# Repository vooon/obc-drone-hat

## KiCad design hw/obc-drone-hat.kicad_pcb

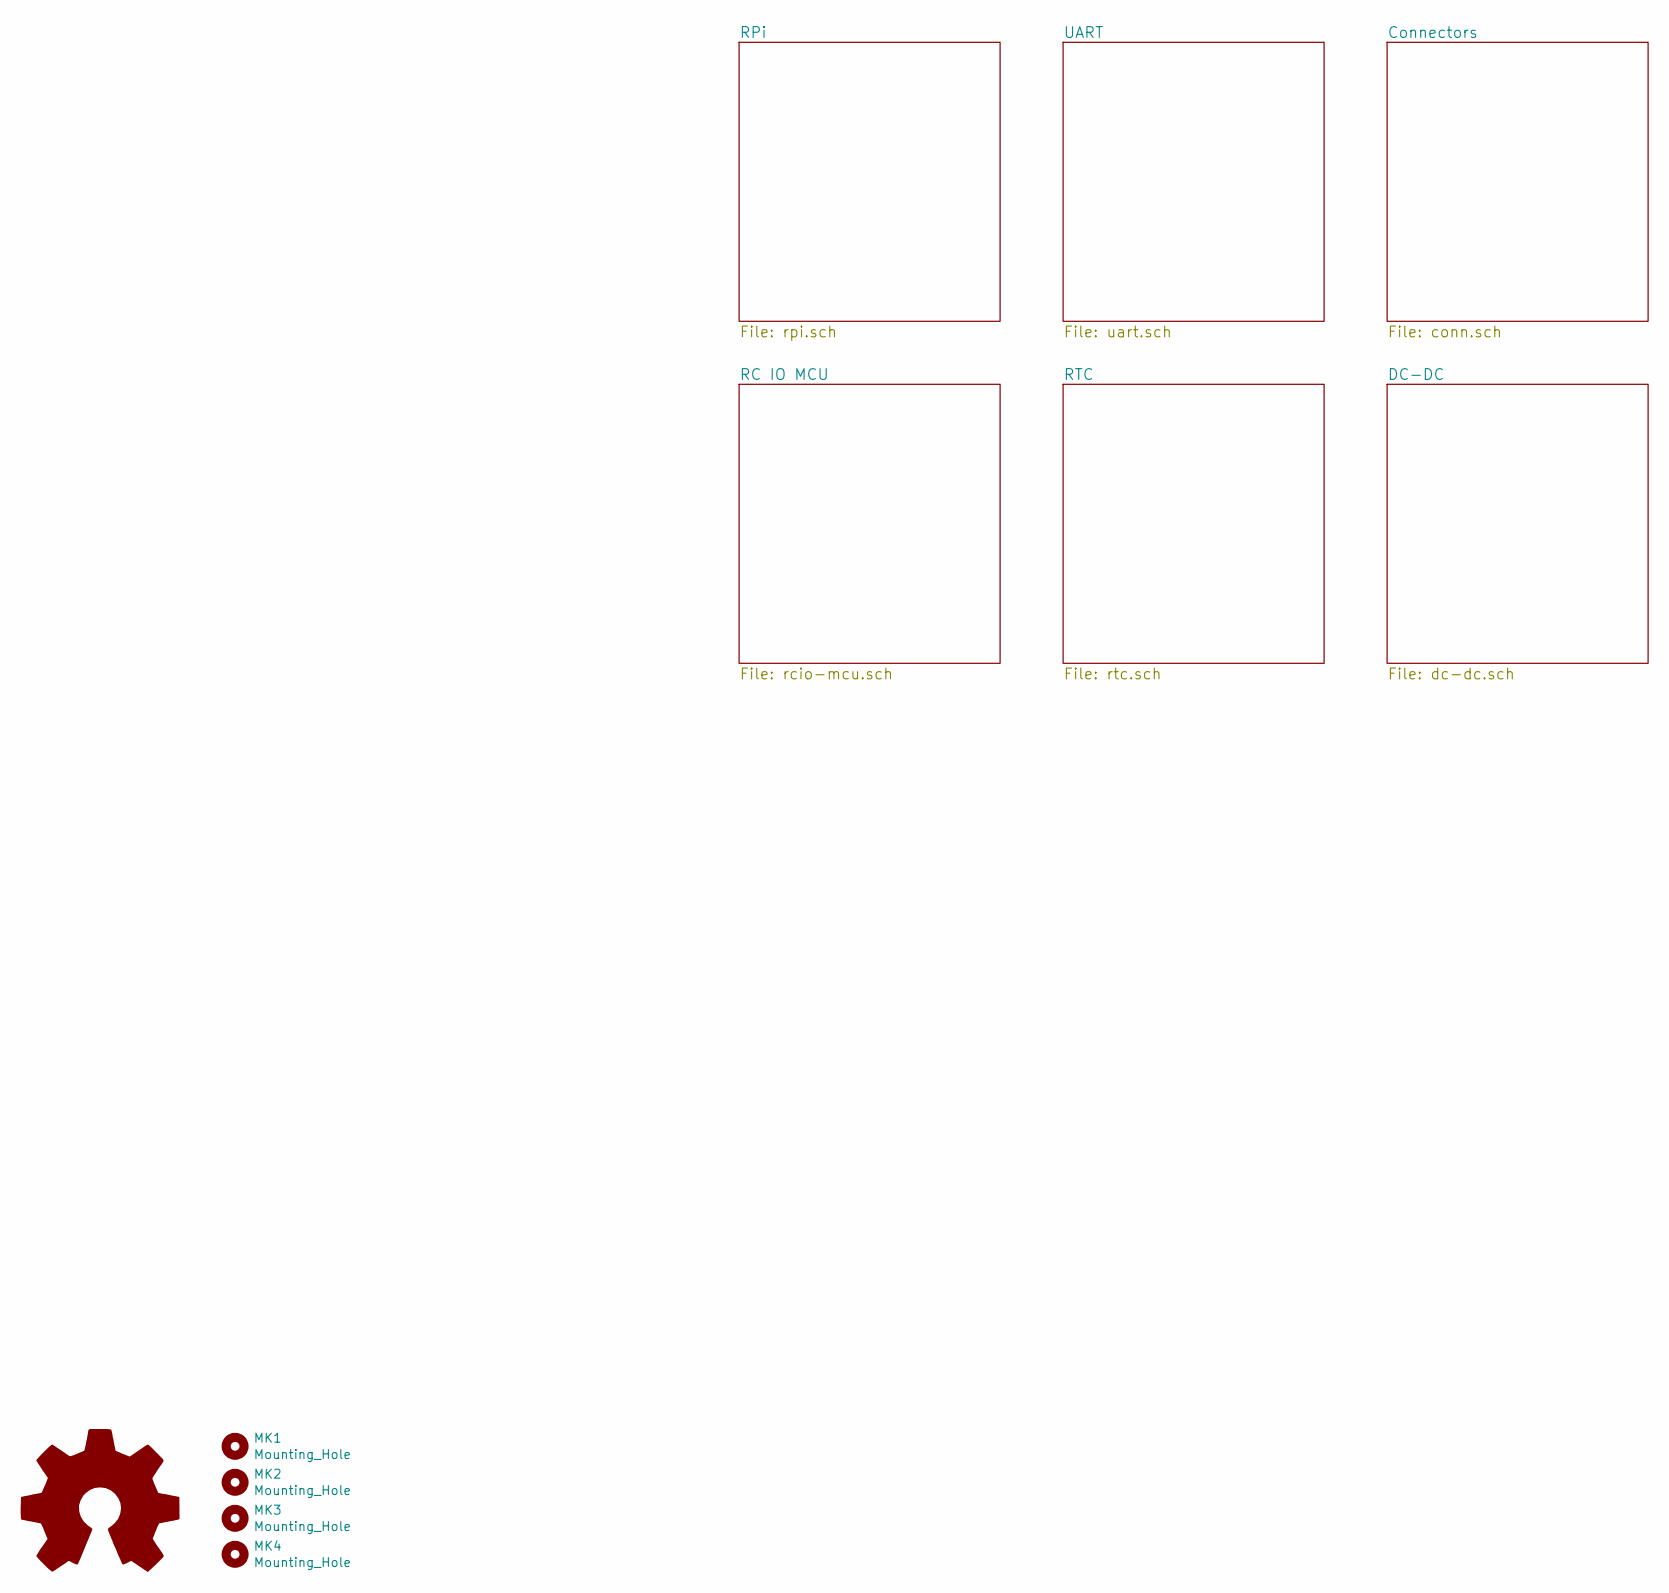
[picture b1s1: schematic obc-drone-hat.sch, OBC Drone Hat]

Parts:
MK1, MK2, MK3, MK4: Mounting_Hole; M2.5_Mounting_Hole

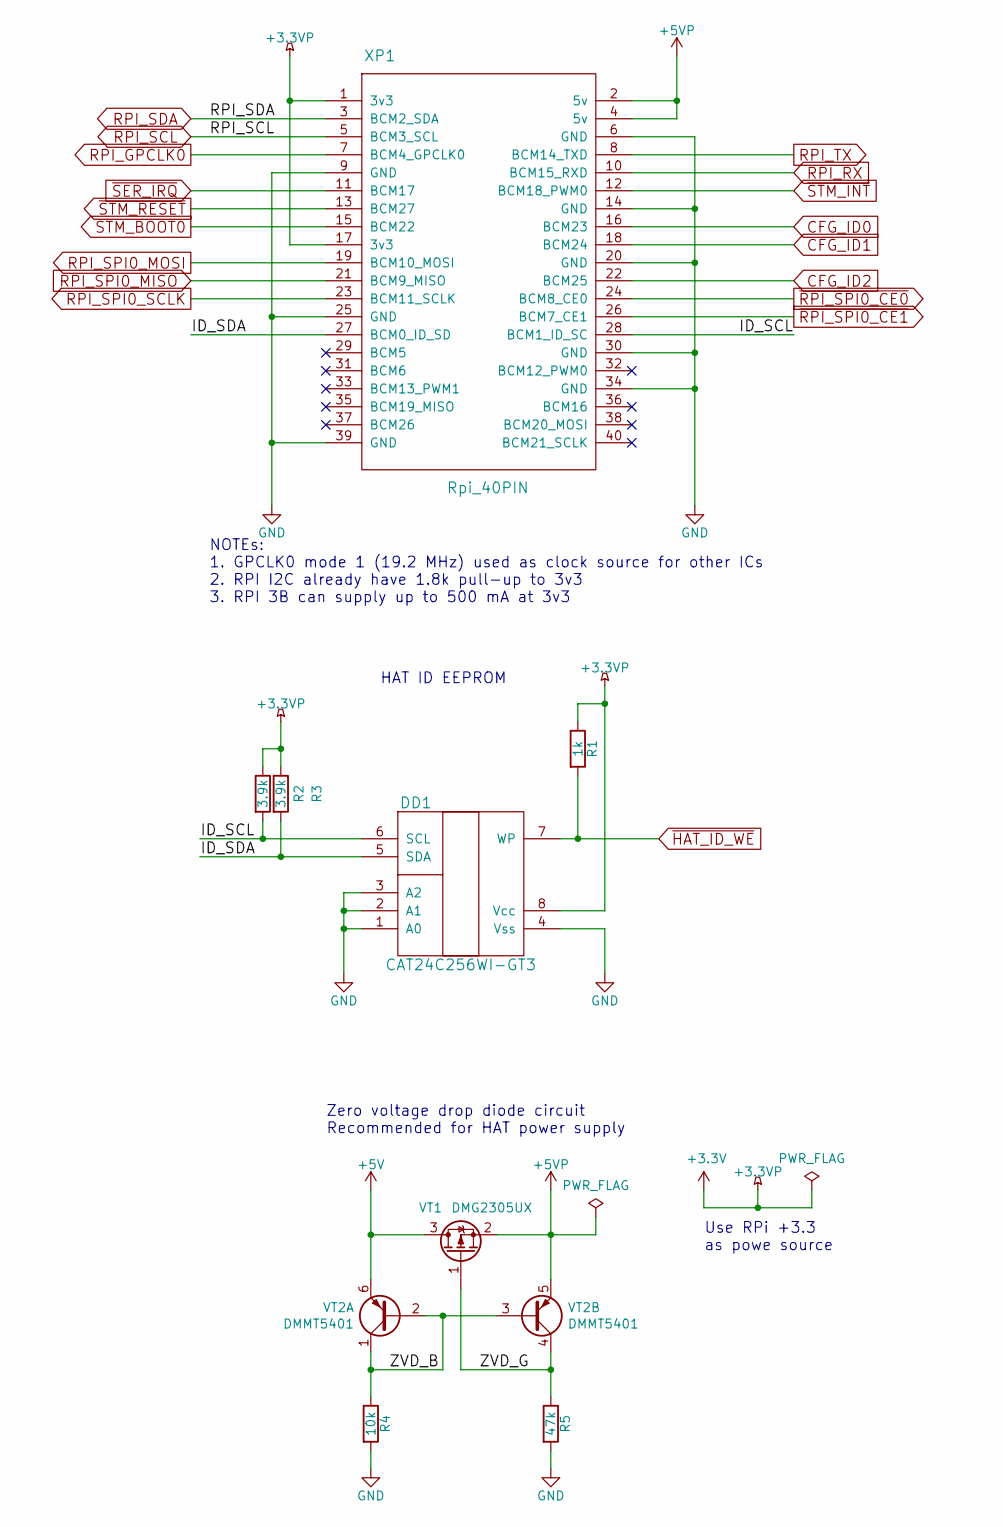
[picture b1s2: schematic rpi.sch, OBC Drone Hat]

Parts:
DD1: CAT24C256WI-GT3; SO-8_5.3x6.2mm_P1.27mm
R1: 1k; R_0603_1608Metric
R2, R3: 3.9k; R_0603_1608Metric
R4: 10k; R_0603_1608Metric
R5: 47k; R_0603_1608Metric
VT1: DMG2305UX; SOT-23_Handsoldering
VT2: DMMT5401; SOT-23-6_Handsoldering
XP1: Rpi_40PIN; RaspberryPi-40Pin_P2.54mm

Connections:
+3.3VP: DD1.8 (Vcc), R1.1, R2.1, R3.1, XP1.1 (3v3), XP1.17 (3v3); also elsewhere on the board
+5VP: VT1.2 (S), VT2.5 (E2), XP1.2 (5v), XP1.4 (5v); also elsewhere on the board
+5Vhat: VT1.3 (D), VT2.6 (E1); also elsewhere on the board
/RPi/ID_SCL: DD1.6 (SCL), R2.2, XP1.28 (BCM1_ID_SC)
/RPi/ID_SDA: DD1.5 (SDA), R3.2, XP1.27 (BCM0_ID_SD)
/RPi/ZVD_B: R4.1, VT2.1 (C1), VT2.2 (B1), VT2.3 (B2)
/RPi/ZVD_G: R5.1, VT1.1 (G), VT2.4 (C2)
CFG_ID0: XP1.16 (BCM23); also elsewhere on the board
CFG_ID1: XP1.18 (BCM24); also elsewhere on the board
CFG_ID2: XP1.22 (BCM25); also elsewhere on the board
GND: DD1.1 (A0), DD1.2 (A1), DD1.3 (A2), DD1.4 (Vss), R4.2, R5.2, XP1.6 (GND), XP1.9 (GND), XP1.14 (GND), XP1.20 (GND), XP1.25 (GND), XP1.30 (GND), XP1.34 (GND), XP1.39 (GND); also elsewhere on the board
RPI_GPCLK0: XP1.7 (BCM4_GPCLK0); also elsewhere on the board
RPI_RX: XP1.10 (BCM15_RXD); also elsewhere on the board
RPI_SCL: XP1.5 (BCM3_SCL); also elsewhere on the board
RPI_SDA: XP1.3 (BCM2_SDA); also elsewhere on the board
RPI_SPI0_MISO: XP1.21 (BCM9_MISO); also elsewhere on the board
RPI_SPI0_MOSI: XP1.19 (BCM10_MOSI); also elsewhere on the board
RPI_SPI0_SCLK: XP1.23 (BCM11_SCLK); also elsewhere on the board
RPI_TX: XP1.8 (BCM14_TXD); also elsewhere on the board
STM_BOOT0: XP1.15 (BCM22); also elsewhere on the board
~HAT_ID_WE: DD1.7 (WP), R1.2; also elsewhere on the board
~RPI_SPI0_CE0: XP1.24 (BCM8_CE0); also elsewhere on the board
~RPI_SPI0_CE1: XP1.26 (BCM7_CE1); also elsewhere on the board
~SER_IRQ: XP1.11 (BCM17); also elsewhere on the board
~STM_INT: XP1.12 (BCM18_PWM0); also elsewhere on the board
~STM_RESET: XP1.13 (BCM27); also elsewhere on the board

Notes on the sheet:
HAT ID EEPROM
NOTEs: 1. GPCLK0 mode 1 (19.2 MHz) used as clock source for other ICs 2. RPI I2C already have 1.8k pull-up to 3v3 3. RPI 3B can supply up to 500 mA at 3v3
Zero voltage drop diode circuit Recommended for HAT power supply
Use RPi +3.3 as powe source

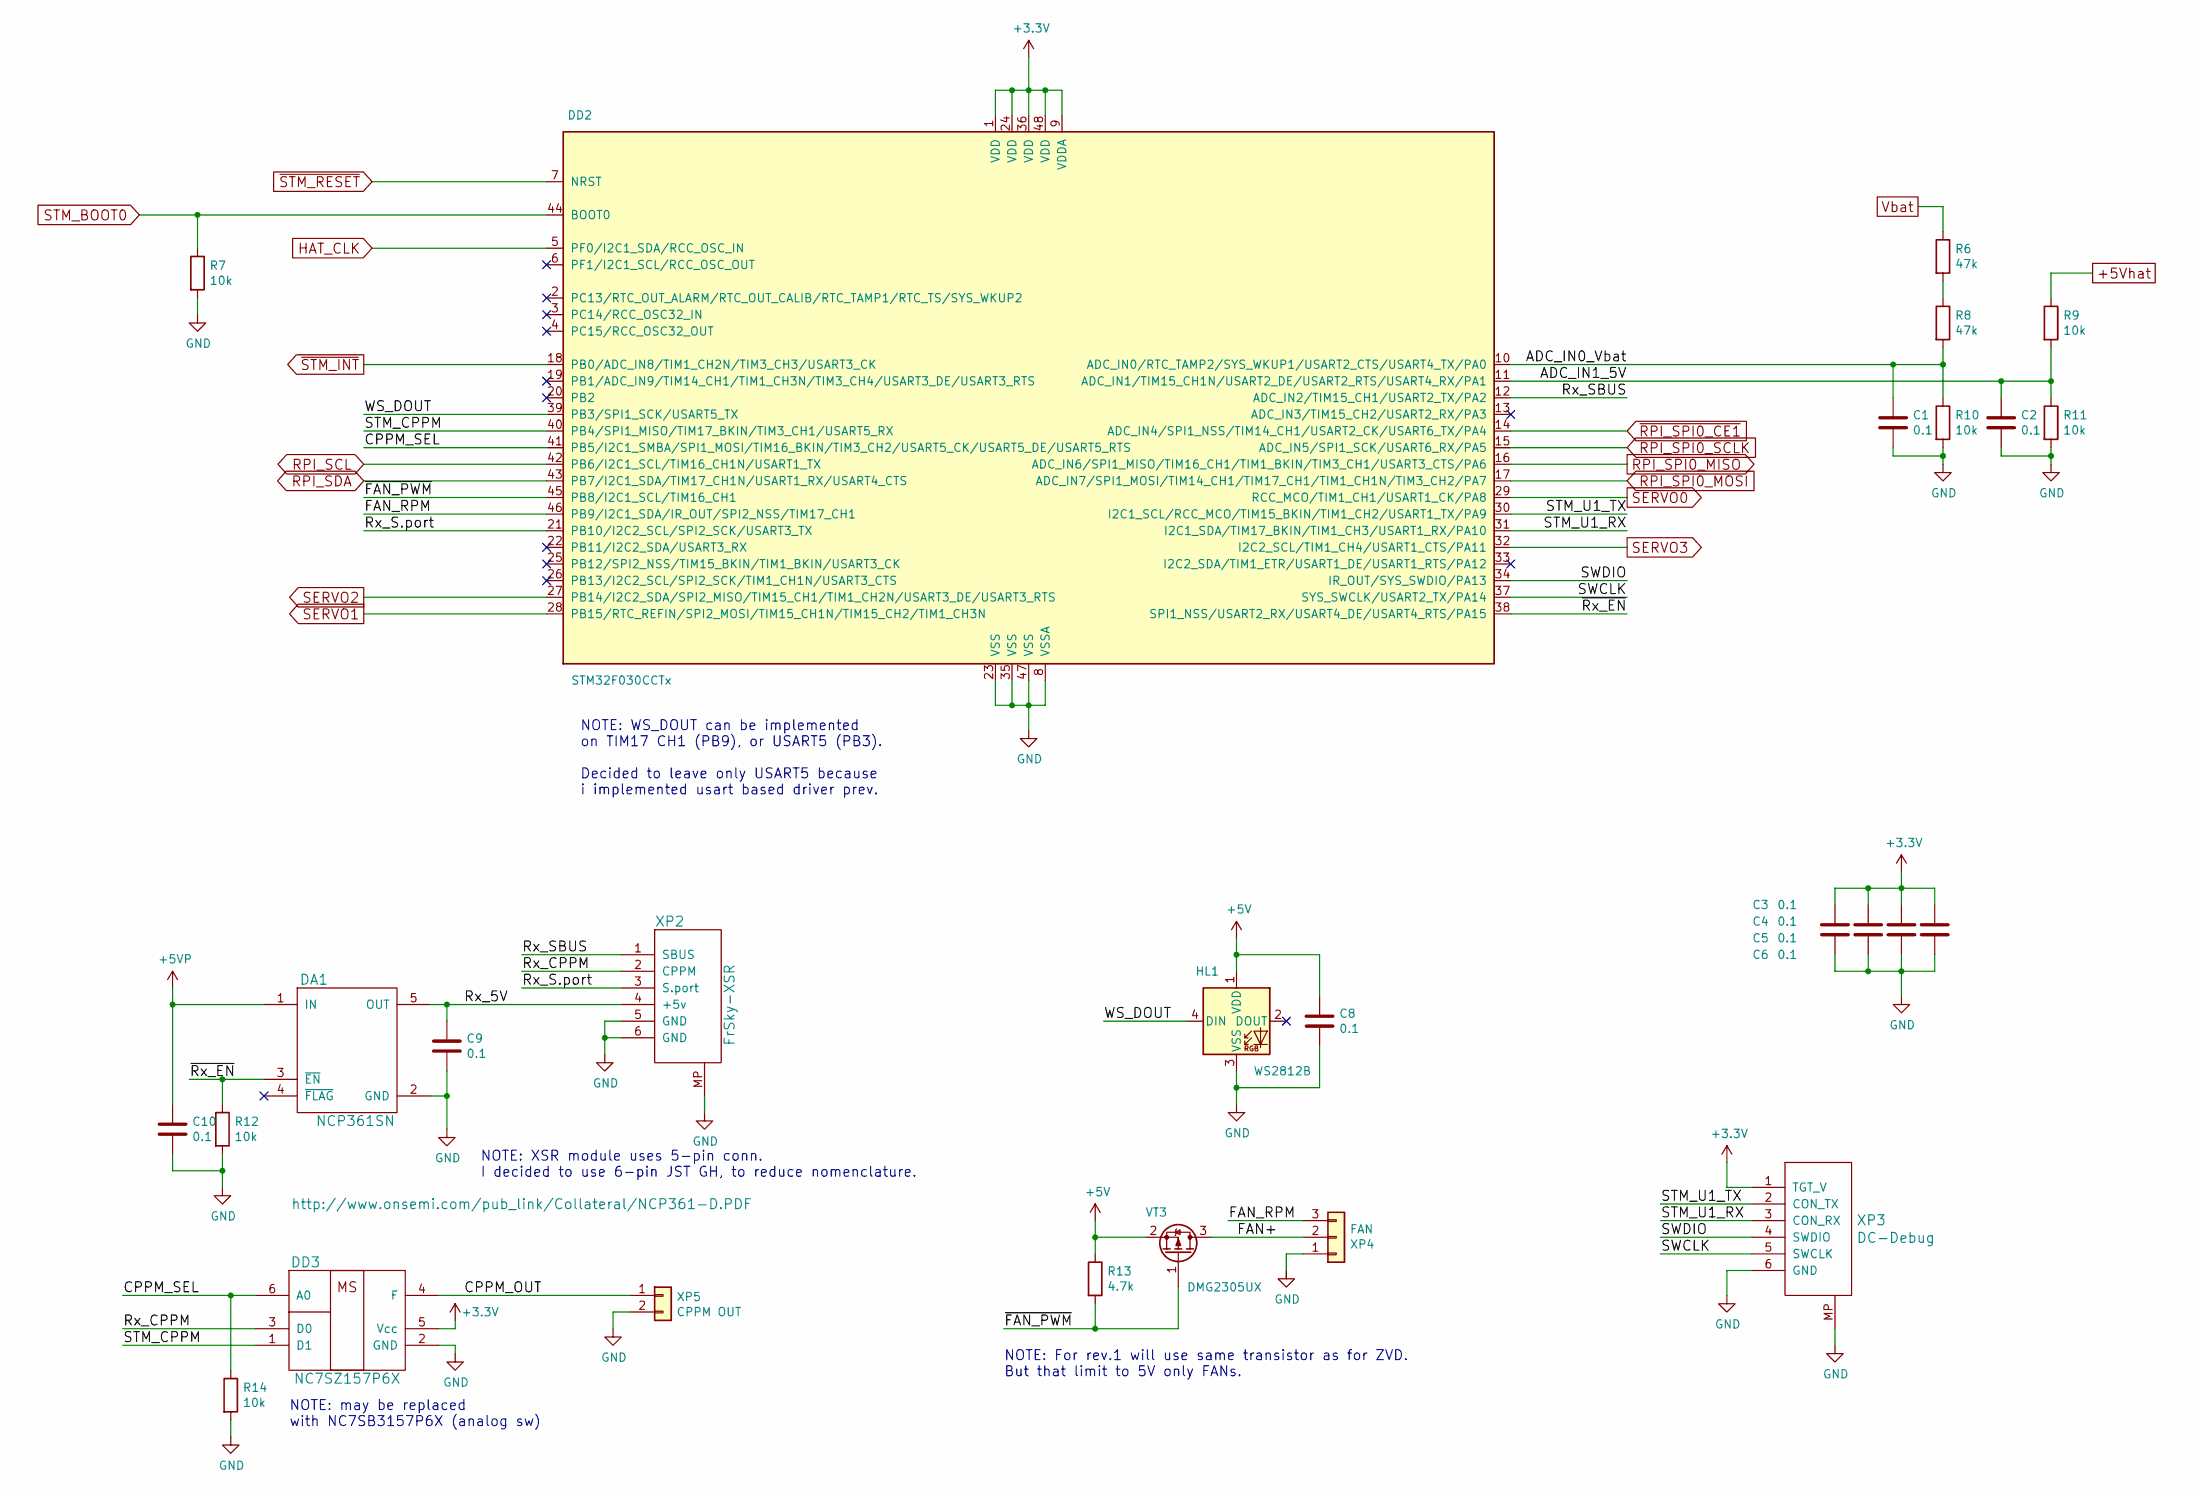
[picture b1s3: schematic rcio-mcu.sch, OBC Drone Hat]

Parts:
C1, C2, C3, C4, C5, C6, C8, C9, C10: 0.1; C_0603_1608Metric
DA1: NCP361SN; SOT-23-5_HandSoldering
DD2: STM32F030CCTx; LQFP-48_7x7mm_P0.5mm
DD3: NC7SZ157P6X; SOT-363_SC-70-6_Handsoldering
HL1: WS2812B; LED_WS2812B_PLCC4_5.0x5.0mm_P3.2mm
R6, R8: 47k; R_0603_1608Metric
R7, R9, R10, R11, R12, R14: 10k; R_0603_1608Metric
R13: 4.7k; R_0603_1608Metric
VT3: DMG2305UX; SOT-23_Handsoldering
XP2: FrSky-XSR; JST_GH_SM06B-GHS-TB_1x06-1MP_P1.25mm_Horizontal
XP3: DC-Debug; JST_GH_BM06B-GHS-TBT_1x06-1MP_P1.25mm_Vertical
XP4: FAN; FanPinHeader_1x03_P2.54mm_Vertical
XP5: CPPM OUT; JST_PH_B2B-PH-K_1x02_P2.00mm_Vertical

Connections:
+3.3VP: C3.1, C4.1, C5.1, C6.1, DD2.1 (VDD), DD2.9 (VDDA), DD2.24 (VDD), DD2.36 (VDD), DD2.48 (VDD), DD3.5 (Vcc), XP3.1 (TGT_V); also elsewhere on the board
+5VP: C10.1, DA1.1 (IN); also elsewhere on the board
+5Vhat: C8.1, HL1.1 (VDD), R9.1, R13.1, VT3.2 (S); also elsewhere on the board
/RC IO MCU/ADC_IN0_Vbat: C1.1, DD2.10 (ADC_IN0/RTC_TAMP2/SYS_WKUP1/USART2_CTS/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), R8.2, R10.1
/RC IO MCU/ADC_IN1_5V: C2.1, DD2.11 (ADC_IN1/TIM15_CH1N/USART2_DE/USART2_RTS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), R9.2, R11.1
/RC IO MCU/CPPM_OUT: DD3.4 (F), XP5.1
/RC IO MCU/CPPM_SEL: DD2.41 (PB5/I2C1_SMBA/SPI1_MOSI/TIM16_BKIN/TIM3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), DD3.6 (A0), R14.1
/RC IO MCU/FAN+: VT3.3 (D), XP4.2
/RC IO MCU/FAN_RPM: DD2.46 (PB9/I2C1_SDA/IR_OUT/SPI2_NSS/TIM17_CH1), XP4.3
/RC IO MCU/Rx_5V: C9.1, DA1.5 (OUT), XP2.4 (+5v)
/RC IO MCU/Rx_CPPM: DD3.3 (D0), XP2.2 (CPPM)
/RC IO MCU/Rx_S.port: DD2.21 (PB10/I2C2_SCL/SPI2_SCK/USART3_TX), XP2.3 (S.port)
/RC IO MCU/Rx_SBUS: DD2.12 (ADC_IN2/TIM15_CH1/USART2_TX/PA2), XP2.1 (SBUS)
/RC IO MCU/STM_CPPM: DD2.40 (PB4/SPI1_MISO/TIM17_BKIN/TIM3_CH1/USART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), DD3.1 (D1)
/RC IO MCU/STM_U1_RX: DD2.31 (I2C1_SDA/TIM17_BKIN/TIM1_CH3/USART1_RX/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), XP3.3 (CON_RX)
/RC IO MCU/STM_U1_TX: DD2.30 (I2C1_SCL/RCC_MCO/TIM15_BKIN/TIM1_CH2/US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), XP3.2 (CON_TX)
/RC IO MCU/SWCLK: DD2.37 (SYS_SWCLK/USART2_TX/PA14), XP3.5 (SWCLK)
/RC IO MCU/SWDIO: DD2.34 (IR_OUT/SYS_SWDIO/PA13), XP3.4 (SWDIO)
/RC IO MCU/WS_DOUT: DD2.39 (PB3/SPI1_SCK/USART5_TX), HL1.4 (DIN)
/RC IO MCU/~FAN_PWM: DD2.45 (PB8/I2C1_SCL/TIM16_CH1), R13.2, VT3.1 (G)
/RC IO MCU/~Rx_EN: DA1.3 (~EN), DD2.38 (SPI1_NSS/USART2_RX/USART4_DE/USART4_RTS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), R12.1
GND: C1.2, C2.2, C3.2, C4.2, C5.2, C6.2, C8.2, C9.2, C10.2, DA1.2 (GND), DD2.8 (VSSA), DD2.23 (VSS), DD2.35 (VSS), DD2.47 (VSS), DD3.2 (GND), HL1.3 (VSS), R7.2, R10.2, R11.2, R12.2, R14.2, XP2.5 (GND), XP2.6 (GND), XP2.MP, XP3.6 (GND), XP3.MP, XP4.1, XP5.2; also elsewhere on the board
HAT_CLK: DD2.5 (PF0/I2C1_SDA/RCC_OSC_IN); also elsewhere on the board
unnamed: R6.2, R8.1
RPI_SCL: DD2.42 (PB6/I2C1_SCL/TIM16_CH1N/USART1_TX); also elsewhere on the board
RPI_SDA: DD2.43 (PB7/I2C1_SDA/TIM17_CH1N/USART1_RX/USART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); also elsewhere on the board
RPI_SPI0_MISO: DD2.16 (ADC_IN6/SPI1_MISO/TIM16_CH1/TIM1_BKIN/T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); also elsewhere on the board
RPI_SPI0_MOSI: DD2.17 (ADC_IN7/SPI1_MOSI/TIM14_CH1/TIM17_CH1/T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); also elsewhere on the board
RPI_SPI0_SCLK: DD2.15 (ADC_IN5/SPI1_SCK/USART6_RX/PA5); also elsewhere on the board
SERVO0: DD2.29 (RCC_MCO/TIM1_CH1/USART1_CK/PA8); also elsewhere on the board
SERVO1: DD2.28 (PB15/RTC_REFIN/SPI2_MOSI/TIM15_CH1N/TIM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); also elsewhere on the board
SERVO2: DD2.27 (PB14/I2C2_SDA/SPI2_MISO/TIM15_CH1/TIM1_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); also elsewhere on the board
SERVO3: DD2.32 (I2C2_SCL/TIM1_CH4/USART1_CTS/PA11); also elsewhere on the board
STM_BOOT0: DD2.44 (BOOT0), R7.1; also elsewhere on the board
Vbat: R6.1; also elsewhere on the board
~RPI_SPI0_CE1: DD2.14 (ADC_IN4/SPI1_NSS/TIM14_CH1/USART2_CK/US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); also elsewhere on the board
~STM_INT: DD2.18 (PB0/ADC_IN8/TIM1_CH2N/TIM3_CH3/USART3_CK); also elsewhere on the board
~STM_RESET: DD2.7 (NRST); also elsewhere on the board

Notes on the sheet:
NOTE: XSR module uses 5-pin conn. I decided to use 6-pin JST GH, to reduce nomenclature.
NOTE: may be replaced with NC7SB3157P6X (analog sw)
NOTE: For rev.1 will use same transistor as for ZVD. But that limit to 5V only FANs.
NOTE: WS_DOUT can be implemented on TIM17 CH1 (PB9), or USART5 (PB3). Decided to leave only USART5 because i implemented usart based driver prev.

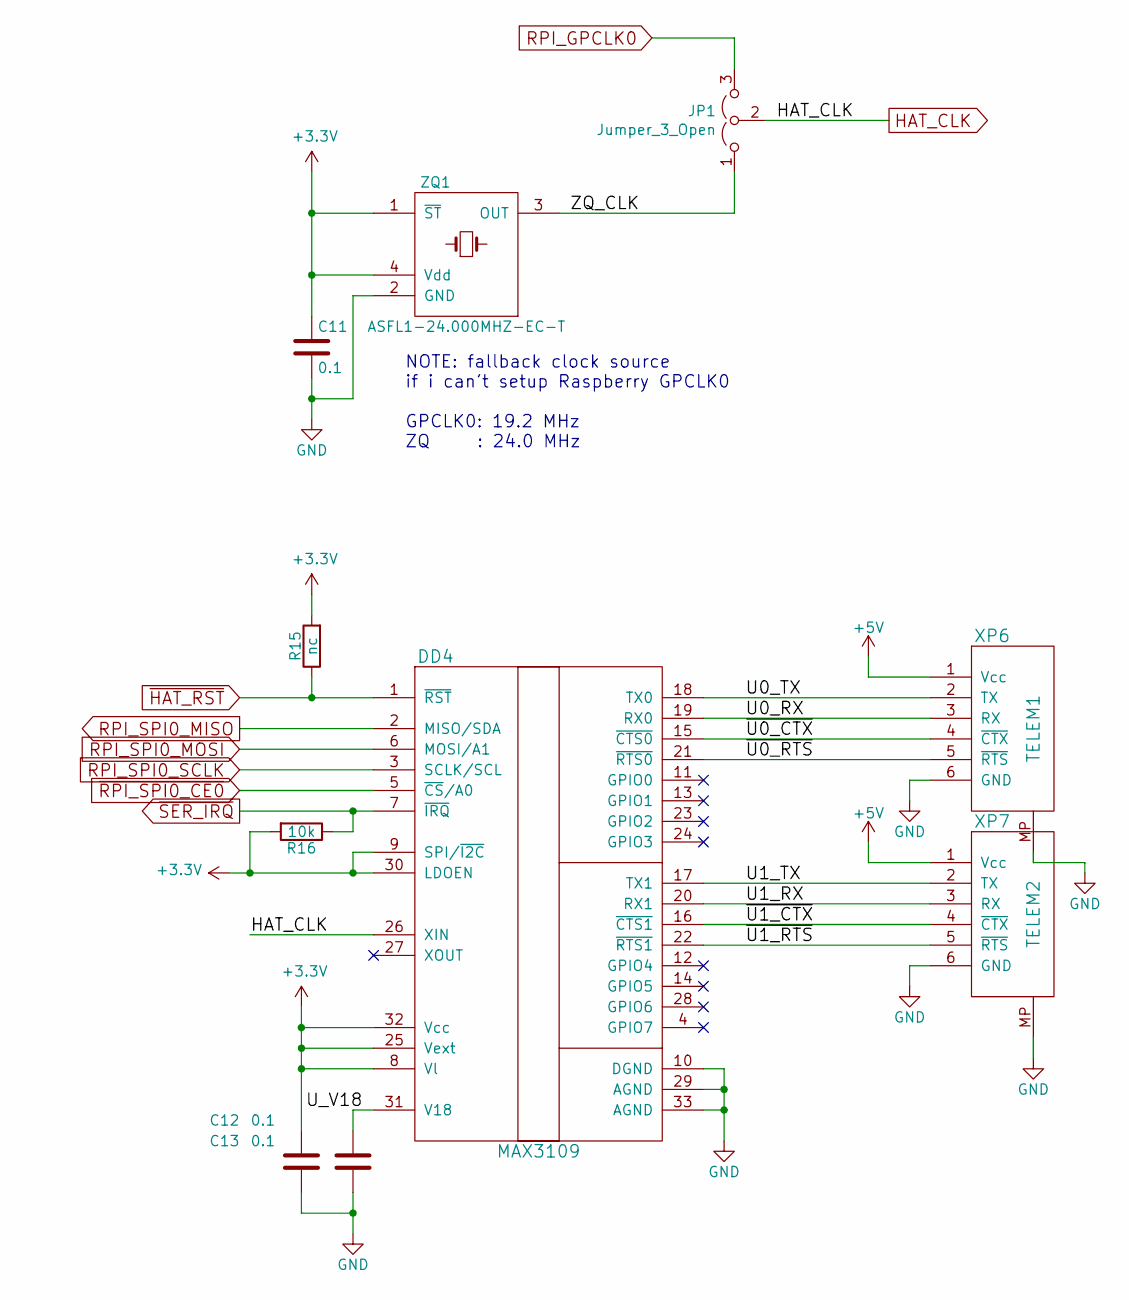
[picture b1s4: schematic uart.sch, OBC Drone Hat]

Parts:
C11, C12, C13: 0.1; C_0603_1608Metric
DD4: MAX3109; QFN-32-1EP_5x5mm_P0.5mm_EP3.45x3.45mm
JP1: Jumper_3_Open; SolderJumper-3_P1.3mm_Open_RoundedPad1.0x1.5mm
R15: nc; R_0603_1608Metric
R16: 10k; R_0603_1608Metric
XP6: TELEM1; JST_GH_SM06B-GHS-TB_1x06-1MP_P1.25mm_Horizontal
XP7: TELEM2; JST_GH_SM06B-GHS-TB_1x06-1MP_P1.25mm_Horizontal
ZQ1: ASFL1-24.000MHZ-EC-T; Crystal_SMD_Abracon_ABM3B-4Pin_5.0x3.2mm

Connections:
+3.3VP: C11.1, C12.1, DD4.8 (Vl), DD4.9 (SPI/~I2C), DD4.25 (Vext), DD4.30 (LDOEN), DD4.32 (Vcc), R15.2, R16.2, ZQ1.1 (~ST), ZQ1.4 (Vdd); also elsewhere on the board
+5Vhat: XP6.1 (Vcc), XP7.1 (Vcc); also elsewhere on the board
/UART/U0_RX: DD4.19 (RX0), XP6.3 (RX)
/UART/U0_TX: DD4.18 (TX0), XP6.2 (TX)
/UART/U1_RX: DD4.20 (RX1), XP7.3 (RX)
/UART/U1_TX: DD4.17 (TX1), XP7.2 (TX)
/UART/U_V18: C13.1, DD4.31 (V18)
/UART/ZQ_CLK: JP1.1 (A), ZQ1.3 (OUT)
/UART/~U0_CTX: DD4.15 (~CTS0), XP6.4 (~CTX)
/UART/~U0_RTS: DD4.21 (~RTS0), XP6.5 (~RTS)
/UART/~U1_CTX: DD4.16 (~CTS1), XP7.4 (~CTX)
/UART/~U1_RTS: DD4.22 (~RTS1), XP7.5 (~RTS)
GND: C11.2, C12.2, C13.2, DD4.10 (DGND), DD4.29 (AGND), DD4.33 (AGND), XP6.6 (GND), XP6.MP, XP7.6 (GND), XP7.MP, ZQ1.2 (GND); also elsewhere on the board
HAT_CLK: DD4.26 (XIN), JP1.2 (C); also elsewhere on the board
RPI_GPCLK0: JP1.3 (B); also elsewhere on the board
RPI_SPI0_MISO: DD4.2 (MISO/SDA); also elsewhere on the board
RPI_SPI0_MOSI: DD4.6 (MOSI/A1); also elsewhere on the board
RPI_SPI0_SCLK: DD4.3 (SCLK/SCL); also elsewhere on the board
~HAT_RST: DD4.1 (~RST), R15.1; also elsewhere on the board
~RPI_SPI0_CE0: DD4.5 (~CS~/A0); also elsewhere on the board
~SER_IRQ: DD4.7 (~IRQ), R16.1; also elsewhere on the board

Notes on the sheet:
NOTE: fallback clock source if i can't setup Raspberry GPCLK0 GPCLK0: 19.2 MHz ZQ : 24.0 MHz

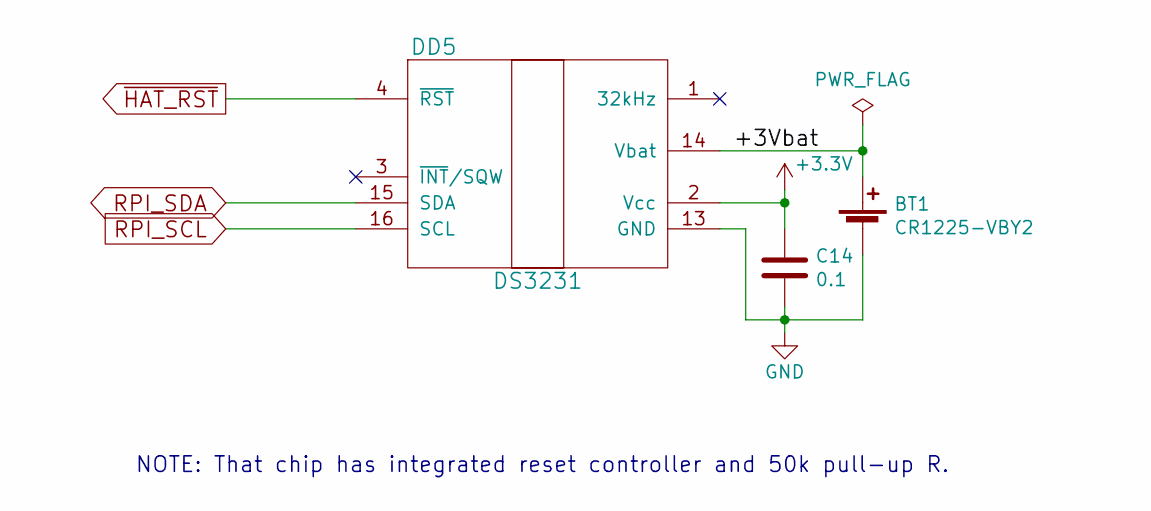
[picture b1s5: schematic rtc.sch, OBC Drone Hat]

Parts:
BT1: CR1225-VBY2
C14: 0.1; C_0603_1608Metric
DD5: DS3231; SOIC-16W_7.5x10.3mm_P1.27mm

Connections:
+3.3VP: C14.1, DD5.2 (Vcc); also elsewhere on the board
/RTC/+3Vbat: BT1.1 (+), DD5.14 (Vbat)
GND: BT1.2 (-), C14.2, DD5.13 (GND); also elsewhere on the board
RPI_SCL: DD5.16 (SCL); also elsewhere on the board
RPI_SDA: DD5.15 (SDA); also elsewhere on the board
~HAT_RST: DD5.4 (~RST); also elsewhere on the board

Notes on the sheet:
NOTE: That chip has integrated reset controller and 50k pull-up R.

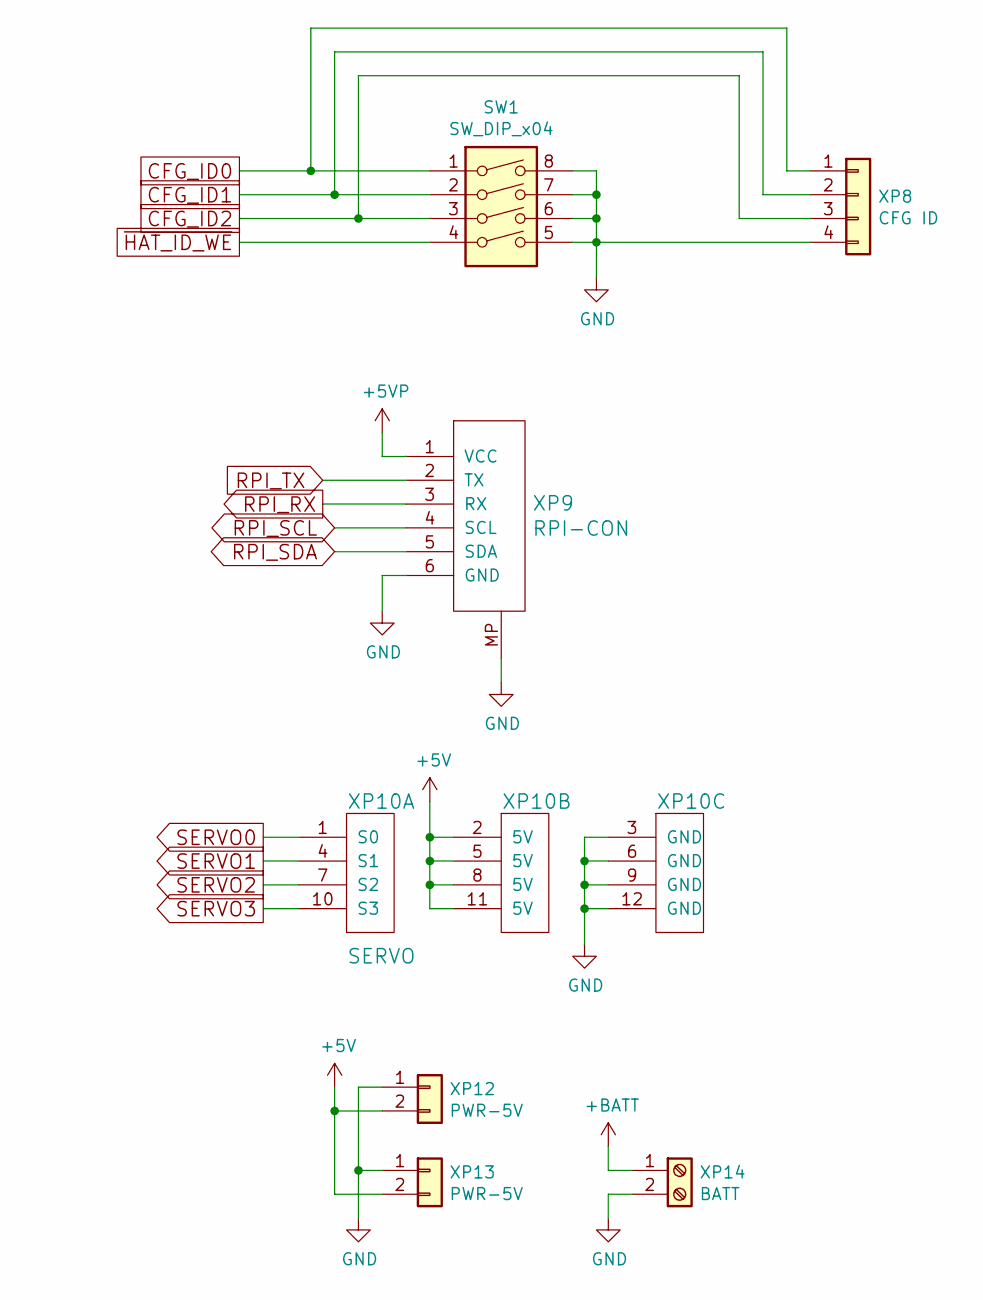
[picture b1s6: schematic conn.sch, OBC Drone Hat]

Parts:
SW1: SW_DIP_x04; SW_DIP_SPSTx04_Slide_9.78x12.34mm_W7.62mm_P2.54mm
XP8: CFG ID; JST_PH_B4B-PH-K_1x04_P2.00mm_Vertical
XP9: RPI-CON; JST_GH_BM06B-GHS-TBT_1x06-1MP_P1.25mm_Vertical
XP10: SERVO; SERVO4
XP12, XP13: PWR-5V; JST_PH_B2B-PH-K_1x02_P2.00mm_Vertical
XP14: BATT; XT30

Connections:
+5VP: XP9.1 (VCC); also elsewhere on the board
+5Vhat: XP10.2 (5V), XP10.5 (5V), XP10.8 (5V), XP10.11 (5V), XP12.2, XP13.2; also elsewhere on the board
CFG_ID0: SW1.1, XP8.1; also elsewhere on the board
CFG_ID1: SW1.2, XP8.2; also elsewhere on the board
CFG_ID2: SW1.3, XP8.3; also elsewhere on the board
GND: SW1.5, SW1.6, SW1.7, SW1.8, XP8.4, XP9.6 (GND), XP9.MP, XP10.3 (GND), XP10.6 (GND), XP10.9 (GND), XP10.12 (GND), XP12.1, XP13.1, XP14.2; also elsewhere on the board
RPI_RX: XP9.3 (RX); also elsewhere on the board
RPI_SCL: XP9.4 (SCL); also elsewhere on the board
RPI_SDA: XP9.5 (SDA); also elsewhere on the board
RPI_TX: XP9.2 (TX); also elsewhere on the board
SERVO0: XP10.1 (S0); also elsewhere on the board
SERVO1: XP10.4 (S1); also elsewhere on the board
SERVO2: XP10.7 (S2); also elsewhere on the board
SERVO3: XP10.10 (S3); also elsewhere on the board
Vbat: XP14.1; also elsewhere on the board
~HAT_ID_WE: SW1.4; also elsewhere on the board

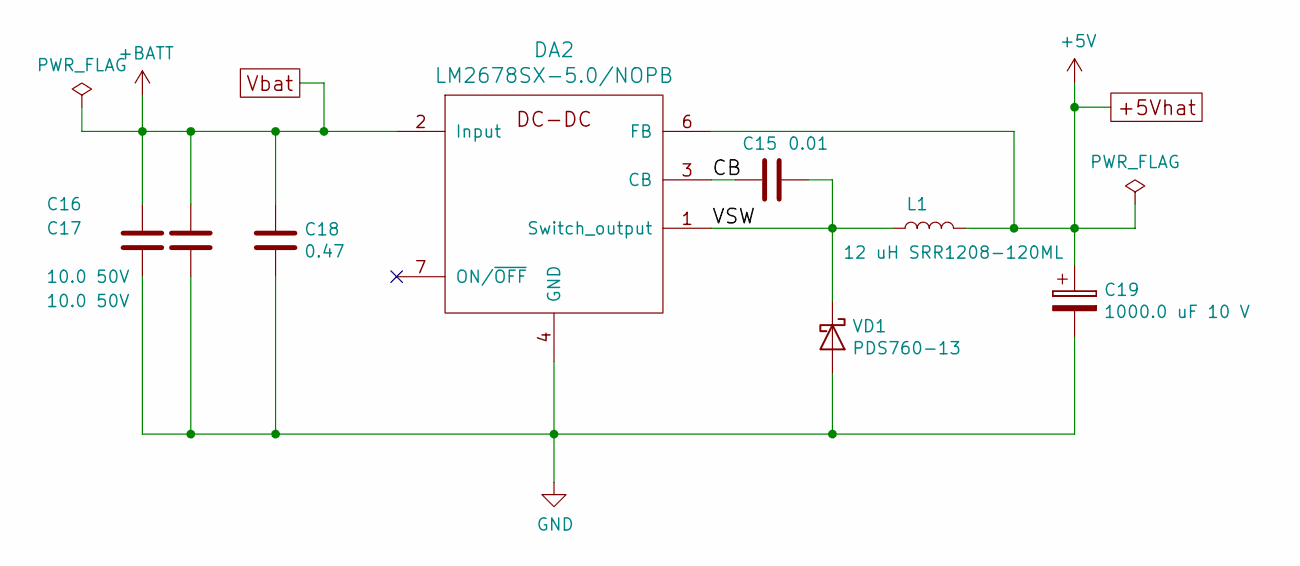
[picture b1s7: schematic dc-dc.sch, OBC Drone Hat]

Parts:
C15: 0.01; C_0603_1608Metric
C16, C17: 10.0 50V; C_1206_3216Metric_Pad1.24x1.80mm_HandSolder
C18: 0.47; C_1206_3216Metric_Pad1.24x1.80mm_HandSolder
C19: 1000.0 uF 10 V; CP_Elec_10x10.5
DA2: LM2678SX-5.0/NOPB; TO-263-7_TabPin4
L1: 12 uH SRR1208-120ML; L_12x12mm_H8mm
VD1: PDS760-13; D-PowerDI-5

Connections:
+5Vhat: C19.1, DA2.6 (FB), L1.2; also elsewhere on the board
/DC-DC/CB: C15.2, DA2.3 (CB)
/DC-DC/VSW: C15.1, DA2.1 (Switch_output), L1.1, VD1.1 (K)
GND: C16.2, C17.2, C18.2, C19.2, DA2.4 (GND), VD1.2 (A); also elsewhere on the board
Vbat: C16.1, C17.1, C18.1, DA2.2 (Input); also elsewhere on the board

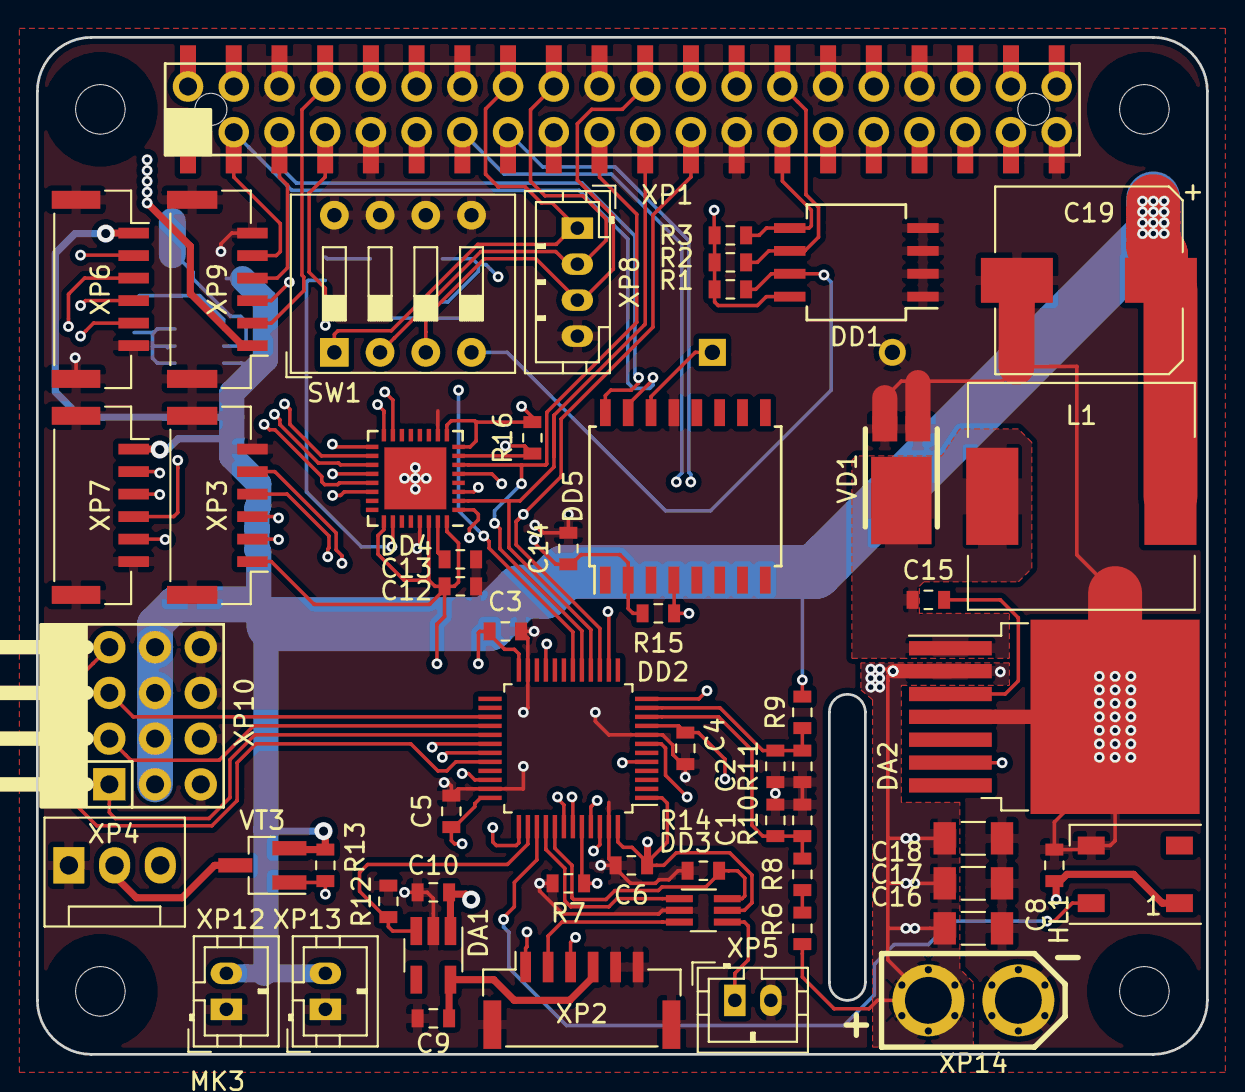
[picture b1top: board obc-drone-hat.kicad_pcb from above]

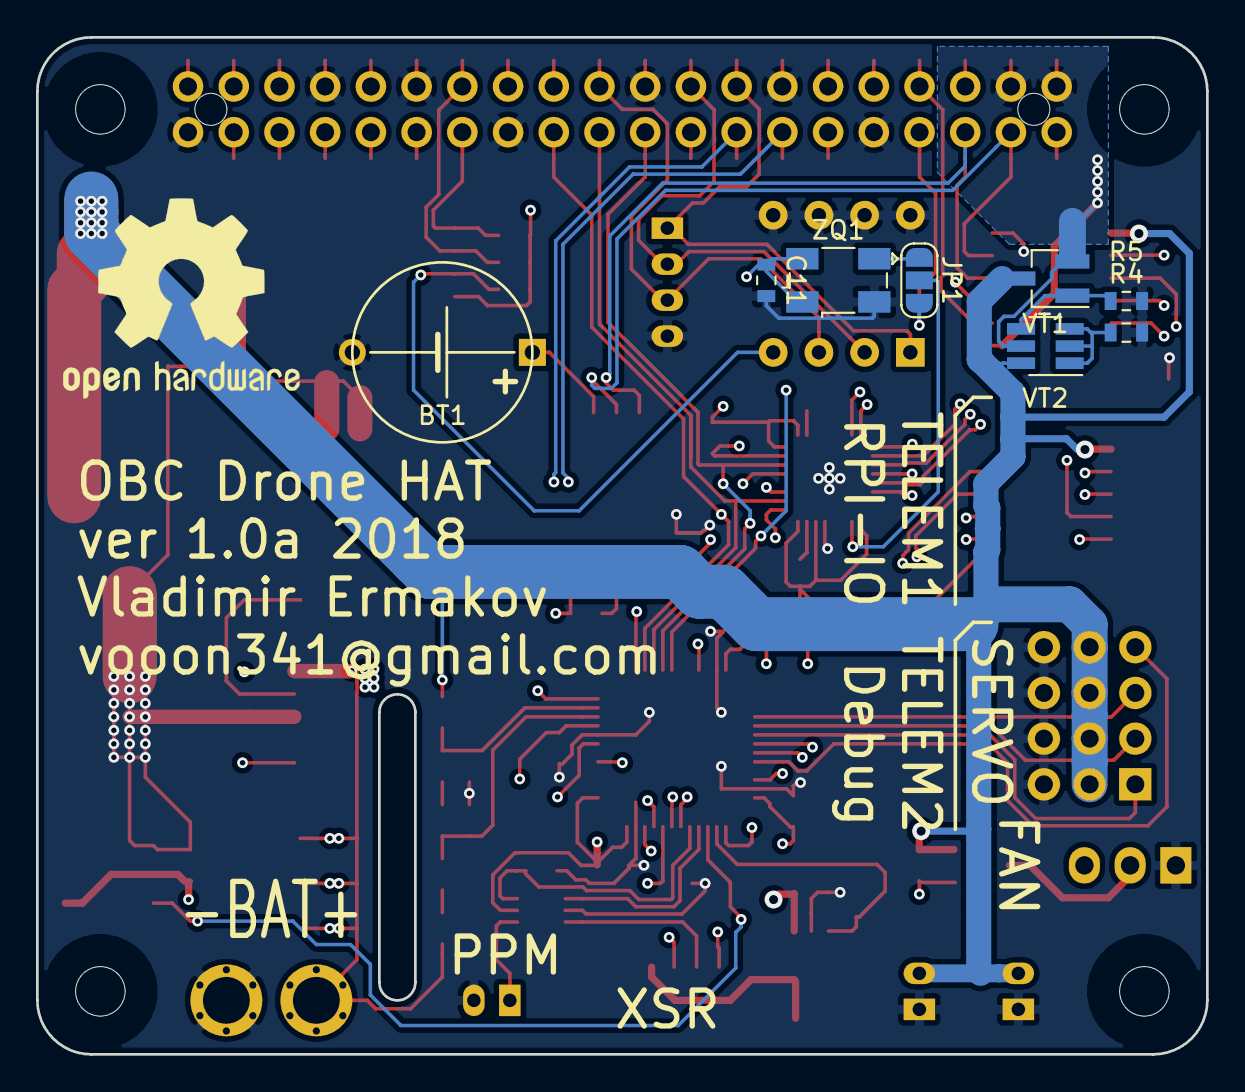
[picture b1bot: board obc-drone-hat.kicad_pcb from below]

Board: 4 copper layers, 65.0 x 56.5 mm, 68 parts (8 on the bottom side), 65 nets.

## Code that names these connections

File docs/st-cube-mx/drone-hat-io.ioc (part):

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Mcu.Name=STM32F030CCTx
Mcu.Package=LQFP48
Mcu.UserName=STM32F030CCTx
PA0.GPIOParameters=GPIO_Label
PA0.GPIO_Label=ADC_IN0_Vbat
PA0.Mode=IN0
PA0.Signal=ADC_IN0
PA1.GPIOParameters=GPIO_Label
PA1.GPIO_Label=ADC_IN1_5V
PA1.Mode=IN1
PA1.Signal=ADC_IN1
PA10.Mode=Asynchronous
PA10.Signal=USART1_RX
PA11.GPIOParameters=GPIO_Label
PA11.GPIO_Label=T1_CH4_SERVO3
PA11.Signal=S_TIM1_CH4
PA13.Mode=Serial_Wire
PA13.Signal=SYS_SWDIO
PA14.Mode=Serial_Wire
PA14.Signal=SYS_SWCLK
PA15.GPIOParameters=GPIO_Label
PA15.GPIO_Label=Rx_EN
PA15.Signal=GPIO_Output
PA2.GPIOParameters=GPIO_Label
PA2.GPIO_Label=U2_TX_SBUS
PA2.Mode=Half_duplex(single_wire_mode)
PA2.Signal=USART2_TX
PA4.Mode=NSS_Signal_Hard_Input
PA4.Signal=SPI1_NSS
PA5.Mode=Full_Duplex_Slave
PA5.Signal=SPI1_SCK
PA6.Mode=Full_Duplex_Slave
PA6.Signal=SPI1_MISO
PA7.Mode=Full_Duplex_Slave
PA7.Signal=SPI1_MOSI
PA8.GPIOParameters=GPIO_Label
PA8.GPIO_Label=T1_CH1_SERVO0
PA8.Signal=S_TIM1_CH1
PA9.Mode=Asynchronous
PA9.Signal=USART1_TX
PB0.GPIOParameters=GPIO_Label
PB0.GPIO_Label=STM_INT
PB0.Signal=GPIO_Output
PB10.GPIOParameters=GPIO_Label
PB10.GPIO_Label=U2_TX_Sport
PB10.Mode=Half_duplex(single_wire_mode)
PB10.Signal=USART3_TX
PB14.GPIOParameters=GPIO_Label
PB14.GPIO_Label=T15_CH1_SERVO2
PB14.Signal=S_TIM15_CH1
PB15.GPIOParameters=GPIO_Label
PB15.GPIO_Label=T15_CH2_SERVO1
PB15.Signal=S_TIM15_CH2
PB3.GPIOParameters=GPIO_Label
PB3.GPIO_Label=U5_TX_WS_DOUT
PB3.Signal=USART5_TX
PB4.GPIOParameters=GPIO_Label
PB4.GPIO_Label=T3_CH1_CPPM
PB4.Signal=S_TIM3_CH1
PB5.GPIOParameters=GPIO_Label
PB5.GPIO_Label=CPPM_SEL
PB5.Signal=GPIO_Output
PB6.Mode=I2C
PB6.Signal=I2C1_SCL
PB7.Mode=I2C
PB7.Signal=I2C1_SDA
PB8.GPIOParameters=GPIO_Label
PB8.GPIO_Label=T16_CH1_FAN_PWM
PB8.Signal=S_TIM16_CH1
PB9.GPIOParameters=GPIO_Label
PB9.GPIO_Label=T17_CH1_WS_DOUT
PB9.Signal=S_TIM17_CH1
PF0-OSC_IN.Mode=HSE-External-Clock-Source
PF0-OSC_IN.Signal=RCC_OSC_IN
RCC.HSE_VALUE=19200000
RCC.SYSCLKFreq_VALUE=48000000
RCC.SYSCLKSource=RCC_SYSCLKSOURCE_PLLCLK

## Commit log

2018-03-19 hw: begin
2018-03-19 docs: add mkdocs
2018-03-19 hw: add sheets
2018-03-19 hw: add CAT24C32 EEPROM symbol
2018-03-19 hw: select pins for serial interrupt and stm control
2018-03-20 hw: update decimal code
2018-03-20 hw: add rpi hat zvd-circuit
2018-03-20 hw: add MAX3109 symbol
2018-03-21 hw: draw hat outline. todo: cuts for flat flex cables, mounting holes
2018-03-21 hw: add uart conns
2018-03-21 hw: add fallback clk source
2018-03-21 hw: add RTC sheet
2018-03-22 hw: add conn and dc-dc sheets
2018-04-01 switch to KiCAD 5 (nightly)
2018-04-01 hw: start stm page
2018-04-01 hw: update libs
2018-04-01 hw: add CPPM source switch
2018-04-01 hw: complete mcu sheet
2018-04-01 hw: add note
2018-04-01 hw: finish conn page
2018-04-08 hw: Use PB9 (TIM17 CH1) for FAN RPM input
2018-04-08 hw: dc-dc page done
2018-04-08 hw: replace STM console and SWD with one connector. Rpi I2C and UART to DroneCode GPS port
2018-04-08 hw: sch ready
2018-04-08 hw: fix ERC
2018-04-08 hw: cvpcb for R,C
2018-04-08 hw: more cvpcb
2018-04-08 hw: only custom packages left unassigned
2018-04-09 hw: wonring on NET
2018-04-09 hw: add mounting holes
2018-04-09 hw: add cut form camera FPC
2018-04-09 hw: add servo conn
2018-04-10 hw: add 40-pin header mod
2018-04-10 hw: add battery input connector
2018-04-10 hw: placement of bigger components
2018-04-10 hw: connect GH mount points with GND, add 3V battery
2018-04-10 hw: move passives
2018-04-10 hw: remove header with unused rpi gpio's, more net labels
2018-04-11 hw: place all components. remove C7 0.1 coupling as not needed.
2018-04-11 hw: prepare to start wiring. add global GND planes
2018-04-14 hw: route dc-dc
2018-04-14 hw: route telem uarts
2018-04-18 hw: route stm debug port
2018-04-18 hw: route pi 5vp
2018-04-18 hw: partial route SPI
2018-04-19 hw: 11 unc left
2018-04-19 hw: routing done
2018-04-19 hw: small route optimizations
2018-04-19 hw: release v1.0a
2018-04-20 release hw ver 1.0a: add gerbers zip and sch pdf
2018-04-20 docs: add 3d render of PCB v1.0
2018-04-20 docs: fix github readme
2018-04-20 docs: add v1 connectors list
